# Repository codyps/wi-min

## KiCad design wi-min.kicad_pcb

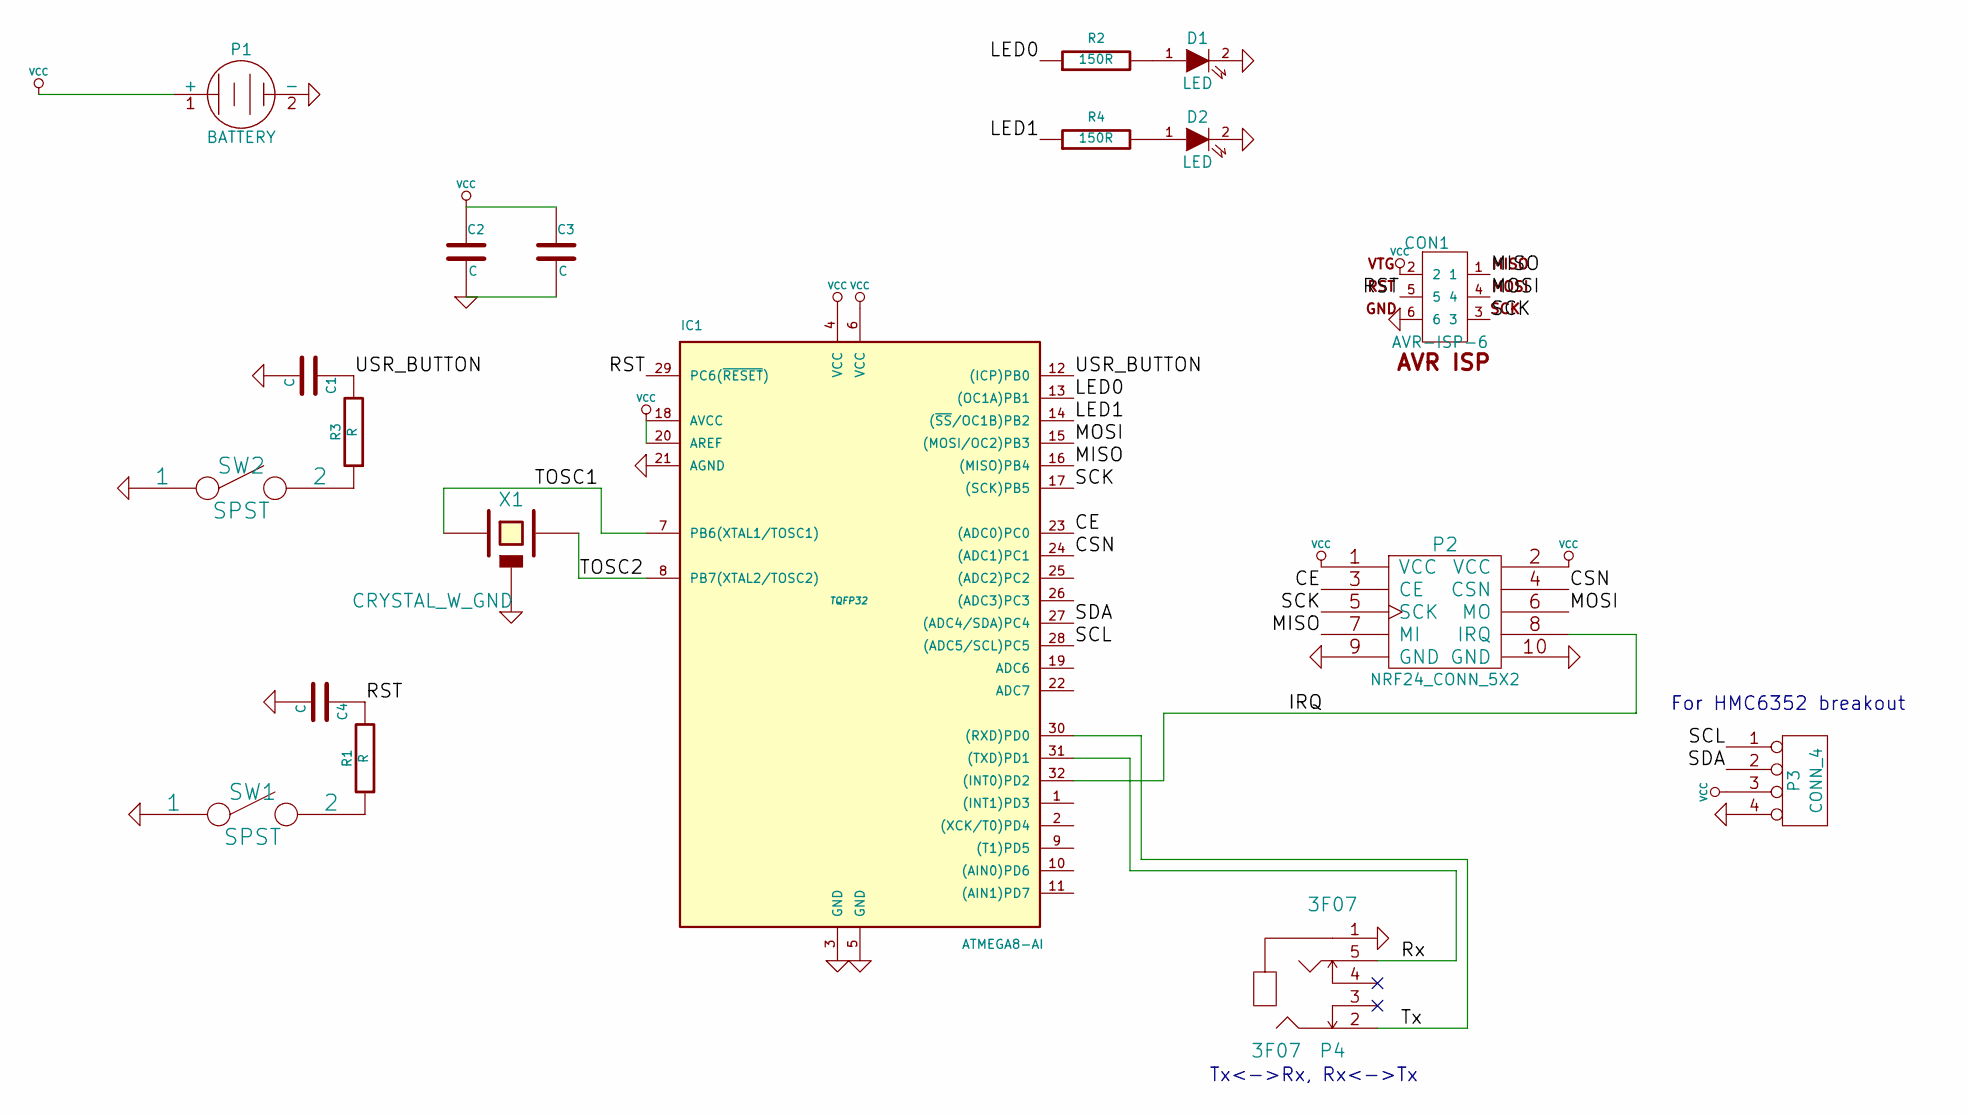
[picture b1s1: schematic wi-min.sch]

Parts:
C1, C2, C3, C4: C
CON1: AVR-ISP-6
D1, D2: LED
IC1: ATMEGA8-AI; TQFP32
P1: BATTERY
P2: NRF24_CONN_5X2
P3: CONN_4
P4: 3F07
R1, R3: R
R2, R4: 150R
SW1, SW2: SPST
X1: CRYSTAL_W_GND

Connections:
/CE: IC1.23 ((ADC0)PC0), P2.3 (CE)
/CSN: IC1.24 ((ADC1)PC1), P2.4 (CSN)
/IRQ: IC1.32 ((INT0)PD2), P2.8 (IRQ)
/LED0: IC1.13 ((OC1A)PB1), R2.1
/LED1: IC1.14 ((~SS~/OC1B)PB2), R4.1
/MISO: CON1.1, IC1.16 ((MISO)PB4), P2.7 (MI)
/MOSI: CON1.4, IC1.15 ((MOSI/OC2)PB3), P2.6 (MO)
/RST: C4.1, CON1.5, IC1.29 (PC6(~RESET~)), R1.2
/Rx: IC1.31 ((TXD)PD1), P4.5
/SCK: CON1.3, IC1.17 ((SCK)PB5), P2.5 (SCK)
/SCL: IC1.28 ((ADC5/SCL)PC5), P3.1
/SDA: IC1.27 ((ADC4/SDA)PC4), P3.2
/TOSC1: IC1.7 (PB6(XTAL1/TOSC1)), X1.1
/TOSC2: IC1.8 (PB7(XTAL2/TOSC2)), X1.2
/Tx: IC1.30 ((RXD)PD0), P4.2
/USR_BUTTON: C1.1, IC1.12 ((ICP)PB0), R3.2
GND: C1.2, C2.2, C3.2, C4.2, CON1.6, D1.2 (K), D2.2 (K), IC1.3 (GND), IC1.5 (GND), IC1.21 (AGND), P1.2 (-), P2.9 (GND), P2.10 (GND), P3.4, P4.1, SW1.1, SW2.1, X1.3
unnamed: R3.1, SW2.2
unnamed: D2.1 (A), R4.2
unnamed: R1.1, SW1.2
unnamed: D1.1 (A), R2.2
VCC: C2.1, C3.1, CON1.2, IC1.4 (VCC), IC1.6 (VCC), IC1.18 (AVCC), IC1.20 (AREF), P1.1 (+), P2.1 (VCC), P2.2 (VCC), P3.3

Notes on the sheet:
Tx<->Rx, Rx<->Tx
For HMC6352 breakout

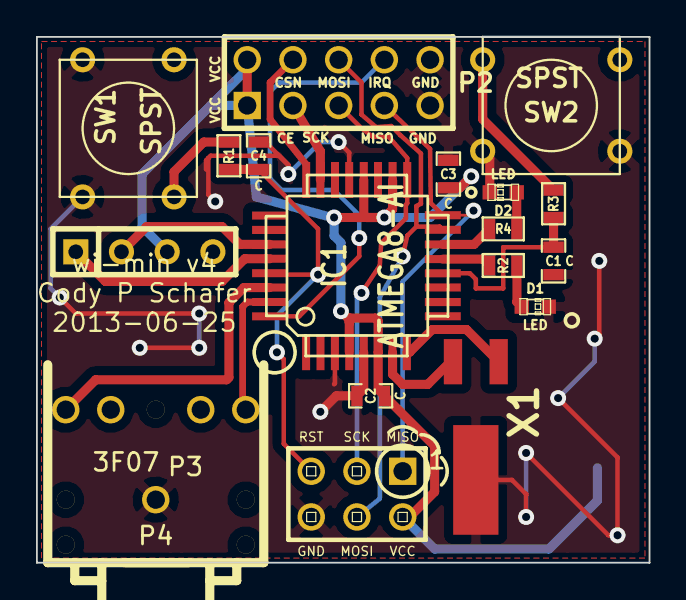
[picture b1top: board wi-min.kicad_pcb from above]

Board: 2 copper layers, 34.0 x 29.2 mm, 19 parts (1 on the bottom side), 22 nets.

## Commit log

2013-05-12 add renders.
2013-06-19 post v2
2013-06-25 v3 sent for fabrication
2013-08-27 post v3 changes
